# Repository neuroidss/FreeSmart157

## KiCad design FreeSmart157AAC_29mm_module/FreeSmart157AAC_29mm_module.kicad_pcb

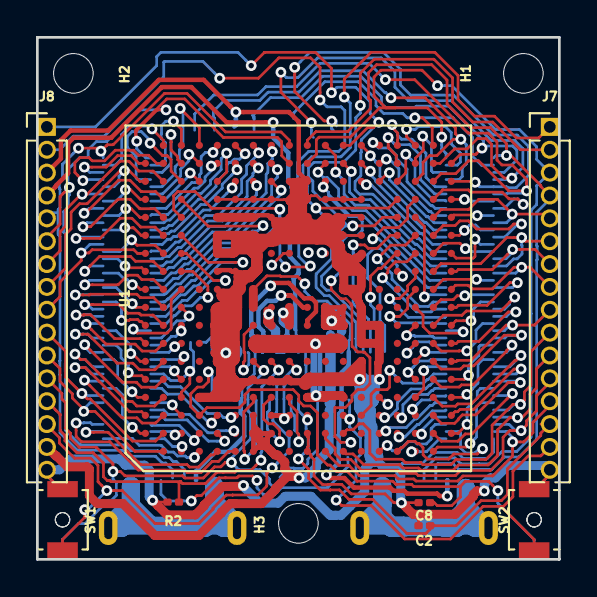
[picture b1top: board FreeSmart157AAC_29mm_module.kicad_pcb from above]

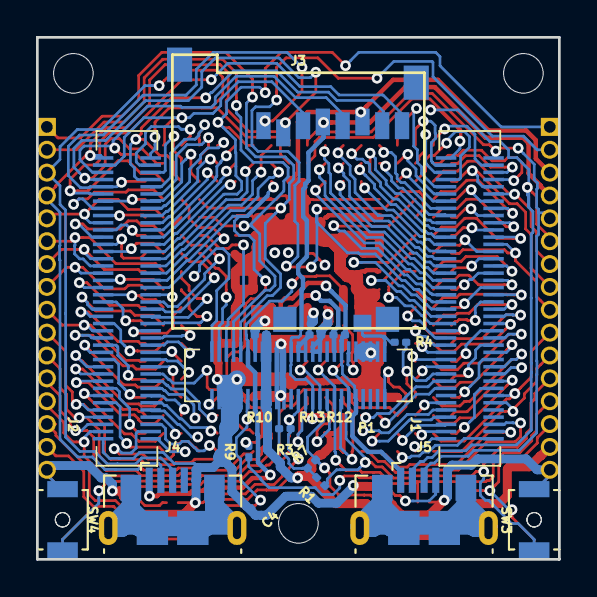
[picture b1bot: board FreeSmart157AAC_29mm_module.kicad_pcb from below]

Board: 2 copper layers, 29.0 x 29.0 mm, 28 parts (17 on the bottom side), 184 nets.

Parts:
C2: 100n; C_0201_0603Metric
C4, C8: 10n; C_0201_0603Metric
H1, H2, H3: MountingHole; MountingHole_2.2mm_M2
J1, J2: Conn_02x40_Odd_Even; HRS_DF40C-80DS-0.4V(51)
J3: 473521001
J4, J5: USB_B_Micro; USB_Micro-B_GCT_USB3076-30-A
J7, J8: Conn_01x16; PinHeader_1x16_P1.27mm_Vertical
P1: DF40C-50DS-0.4V(51); HRS_DF40C-50DS-0.4V(51)
R1, R2, R7: 1k; R_0201_0603Metric
R3, R4, R9, R10, R12, R13: 0; R_0201_0603Metric
SW1: SW_BOOT0; SW_SPST_B3U-1000P-B
SW2: SW_NRST; SW_SPST_B3U-1000P-B
SW3: SW_BOOT2; SW_SPST_B3U-1000P-B
SW4: SW_PMIC_PONKEYN; SW_SPST_B3U-1000P-B
U1: OSD32MP157C-512M-BAA; OSD32MP15x_BGA-302_19.0x19.0mm_Layout18x18_P1.0mm_Ball0.5mm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

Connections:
3V3: J3.4, J8.4, P1.22, P1.27, U1.H3, U1.J3
5V_VIN: J8.15, P1.33, P1.34, P1.35, P1.36, R10.1, U1.G1, U1.G2, U1.G3, U1.H1, U1.H2
A2: J1.15, U1.A2
A3: J1.19, U1.A3
A4: J1.23, U1.A4
A5: J1.27, U1.A5
A6: J1.31, U1.A6
A7: J1.35, U1.A7
A8: J1.39, U1.A8
A9: J1.43, U1.A9
A10: J1.47, U1.A10
A11: J1.51, U1.A11
A12: J1.55, J8.9, U1.A12
A13: J1.59, U1.A13
A14: J1.63, U1.A14
A15: J1.67, U1.A15
A16: J1.71, J8.8, U1.A16
A17: J1.75, U1.A17
B1: J1.11, J8.11, U1.B1
B2: J1.13, J8.10, U1.B2
B3: J1.17, U1.B3
B4: J1.21, U1.B4
B5: J1.25, U1.B5
B6: J1.29, U1.B6
B7: J1.33, U1.B7
B8: J1.37, U1.B8
B9: J1.41, U1.B9
B10: J1.45, U1.B10
B11: J1.49, U1.B11
B12: J1.53, U1.B12
B13: J1.57, U1.B13
B14: J1.61, U1.B14
B15: J1.65, U1.B15
B16: J1.69, J8.7, U1.B16
B17: J1.73, U1.B17
B18: J1.77, U1.B18
C1: J1.2, U1.C1
C2: J1.4, U1.C2
C3: J1.12, U1.C3
C4: J1.20, R4.2, U1.C4
C5: J1.22, U1.C5
C6: J1.24, U1.C6
C7: J1.26, U1.C7
C8: J1.28, U1.C8
C9: J1.30, U1.C9
C10: J1.32, U1.C10
C11: J1.34, U1.C11
C12: J1.36, U1.C12
C13: J1.38, U1.C13
C14_PG11_UART4_TX: J1.40, J8.2, U1.C14
C15: J1.42, U1.C15
C16: J1.74, U1.C16
C17: J1.76, U1.C17
C18: J1.78, U1.C18
D1: J1.1, U1.D1
D2: J1.6, U1.D2
D16: J1.68, U1.D16
D17: J1.70, U1.D17
D18: J1.72, U1.D18
E1: J1.3, U1.E1
E2: J1.8, U1.E2
E3: J1.16, U1.E3
E16: J1.62, U1.E16
E17: J1.64, U1.E17
E18: J1.66, U1.E18
F1: J1.5, U1.F1
F2: J1.10, U1.F2
F3: J1.18, U1.F3
F16: J1.56, U1.F16
F17: J1.58, U1.F17
F18: J1.60, U1.F18
G6_BOOT2: J8.12, P1.12, R1.1, SW3.1, U1.G6
G16: J1.50, U1.G16
G17: J1.52, U1.G17
G18: J1.54, U1.G18
H6_BOOT1: J8.13, P1.16, R2.1, U1.H6
H16: J1.44, U1.H16
H17: J1.46, U1.H17
H18: J1.48, U1.H18
J6_BOOT0: J8.14, P1.20, R7.1, SW1.1, U1.J6
J17_USB_DM2: J1.80, J5.2, J8.6, U1.J17
J18_USB_DP2: J1.79, J5.3, J8.5, U1.J18
K1_VSSA: C2.2, C4.2, C8.2, J2.2, J3.6, J4.5, J5.5, J7.16, J8.3, J8.16, P1.3, P1.5, P1.7, P1.9, P1.42, P1.44, P1.46, P1.48, R2.2, SW1.2, SW2.2, SW3.2, SW4.2, U1.D4, U1.E4, U1.E5, U1.E6, U1.E7, U1.E8, U1.E9, U1.E10, U1.E11, U1.E12, U1.E13, U1.E14, U1.E15, U1.F4, U1.F5, U1.F6, U1.F7, U1.F8, U1.F9, U1.F10, U1.F11, U1.F12, U1.F13, U1.F14, U1.F15, U1.G5, U1.G11, U1.G12, U1.G13, U1.G14, U1.G15, U1.H5, U1.H13, U1.H14, U1.H15, U1.J5, U1.J13, U1.J14, U1.J15, U1.J16, U1.K1, U1.K2, U1.K5, U1.K13, U1.K14, U1.K15, U1.K16, U1.L5, U1.L13, U1.L14, U1.L15, U1.M5, U1.M10, U1.M11, U1.M12, U1.M13, U1.M14, U1.M15, U1.N5, U1.N6, U1.N7, U1.N8, U1.N9, U1.N10, U1.N11, U1.N12, U1.N13, U1.N14, U1.N15, U1.P5, U1.P6, U1.P7, U1.P8
K3_VBAT: C2.1, J7.14, P1.26, R3.1, U1.K3
K9_OTG_VBUS: P1.15, R12.2, U1.K9
K17_USB_DP1: J2.79, J4.3, J7.3, U1.K17
K18_USB_DM1: J2.80, J4.2, J7.4, U1.K18
L1_ANA0: J2.4, J7.13, U1.L1
L2_ANA1: J2.6, J7.12, U1.L2
L16: J2.45, R9.2, U1.L16
L17: J2.47, U1.L17
L18: J2.49, U1.L18
M1_VDDA: J2.8, J7.11, U1.M1
M2_VREF+: J2.10, J7.10, U1.M2
M3_NRST: C4.1, J7.15, P1.40, SW2.1, U1.M3
M17: J2.51, U1.M17
M18_PB2_UART4_RX: J2.53, J8.1, U1.M18
N3: J2.19, U1.N3
N16_DSI_CKP: J2.55, U1.N16
N17_DSI_D1P: J2.57, U1.N17
N18_DSI_D1N: J2.59, U1.N18
P1: J2.5, U1.P1
P2: J2.11, U1.P2
P3: J2.17, U1.P3
P4_EEPROM_WP: P1.50, U1.P4
P16_DSI_CKN: J2.61, U1.P16
P17_DSI_D0P: J2.63, U1.P17
P18_DSI_D0N: J2.65, U1.P18
PMIC_BSTIN: P1.37, R10.2, U1.L8, U1.L9, U1.M8, U1.M9
PMIC_BSTOUT: P1.23, P1.25, R13.1, U1.J8, U1.J9
PMIC_LDO1: P1.24, U1.J4
PMIC_LDO2: P1.14, U1.G4
PMIC_LDO5: P1.11, U1.G8
PMIC_LDO6: P1.18, U1.H4
PMIC_PONKEYN: C8.1, P1.2, SW4.1, U1.D3
PMIC_SWIN: P1.19, P1.21, R13.2, U1.H8, U1.H9
PMIC_SWOUT: J4.1, P1.38, P1.39, U1.G9, U1.G10
PMIC_VBUSOTG: J5.1, P1.10, P1.13, R12.1, U1.K8
R1: J2.3, U1.R1
R2: J2.9, U1.R2
R3: J2.15, U1.R3
R11_NJTRST: P1.49, U1.R11
R12_JTDO-TRACESWO: P1.47, U1.R12
R13_JTDI: P1.45, U1.R13
R14_JTMS-SWDIO: J7.2, P1.43, U1.R14
R15_JTCK-SWCLK: J7.1, P1.41, U1.R15
R16: J2.67, U1.R16
R17: J2.69, U1.R17
R18: J2.71, U1.R18
SDMMC1_DETECT: J3.9, P1.1, R4.1
T1: J2.1, U1.T1
T2: J2.7, U1.T2
T3: J2.13, U1.T3
T4: J2.21, U1.T4
T5: J2.23, U1.T5
T6: J2.25, U1.T6
T7: J2.27, U1.T7
T8: J2.29, U1.T8
T9: J2.31, U1.T9
T10: J2.33, U1.T10
T11: J2.35, U1.T11
T12: J2.37, U1.T12
T13: J2.39, U1.T13
T14: J2.41, U1.T14
T15: J2.43, U1.T15
T16_PC8_SDMMC1_D0: J2.73, J3.7, U1.T16
T17: J2.75, U1.T17
T18: J2.77, U1.T18
U1: J2.12, U1.U1
U2: J2.14, U1.U2
U3: J2.18, U1.U3
U4: J2.22, U1.U4
U5: J2.26, U1.U5
U6: J2.30, U1.U6
U7: J2.34, U1.U7
U8: J2.38, U1.U8
U9: J2.42, U1.U9
U10: J2.46, U1.U10
U11: J2.50, J7.6, U1.U11
U12: J2.54, U1.U12
U13: J2.58, U1.U13
U14: J2.62, J7.5, U1.U14
U15: J2.66, U1.U15
U16_PC9_SDMMC1_D1: J2.70, J3.8, U1.U16
U17_PC11_SDMMC1_D3: J2.74, J3.2, U1.U17
U18_PD2_SDMMC1_CMD: J2.78, J3.3, U1.U18
USBID2: J5.4, R9.1
V2: J2.16, U1.V2
V3: J2.20, U1.V3
V4: J2.24, U1.V4
V5: J2.28, U1.V5
V6: J2.32, J7.9, U1.V6
V7: J2.36, U1.V7
V8: J2.40, U1.V8
V9: J2.44, U1.V9
V10: J2.48, J7.8, U1.V10
V11: J2.52, J7.7, U1.V11
V12: J2.56, U1.V12
V13: J2.60, U1.V13
V14: J2.64, U1.V14
V15: J2.68, U1.V15
V16_PC10_SDMMC1_D2: J2.72, J3.1, U1.V16
V17_PC12_SDMMC1_CK: J2.76, J3.5, U1.V17
VDD: P1.29, P1.30, P1.31, P1.32, R1.2, R3.2, R7.2, U1.G7, U1.H7, U1.J7, U1.K4, U1.K7, U1.L4, U1.L7, U1.M4, U1.M7

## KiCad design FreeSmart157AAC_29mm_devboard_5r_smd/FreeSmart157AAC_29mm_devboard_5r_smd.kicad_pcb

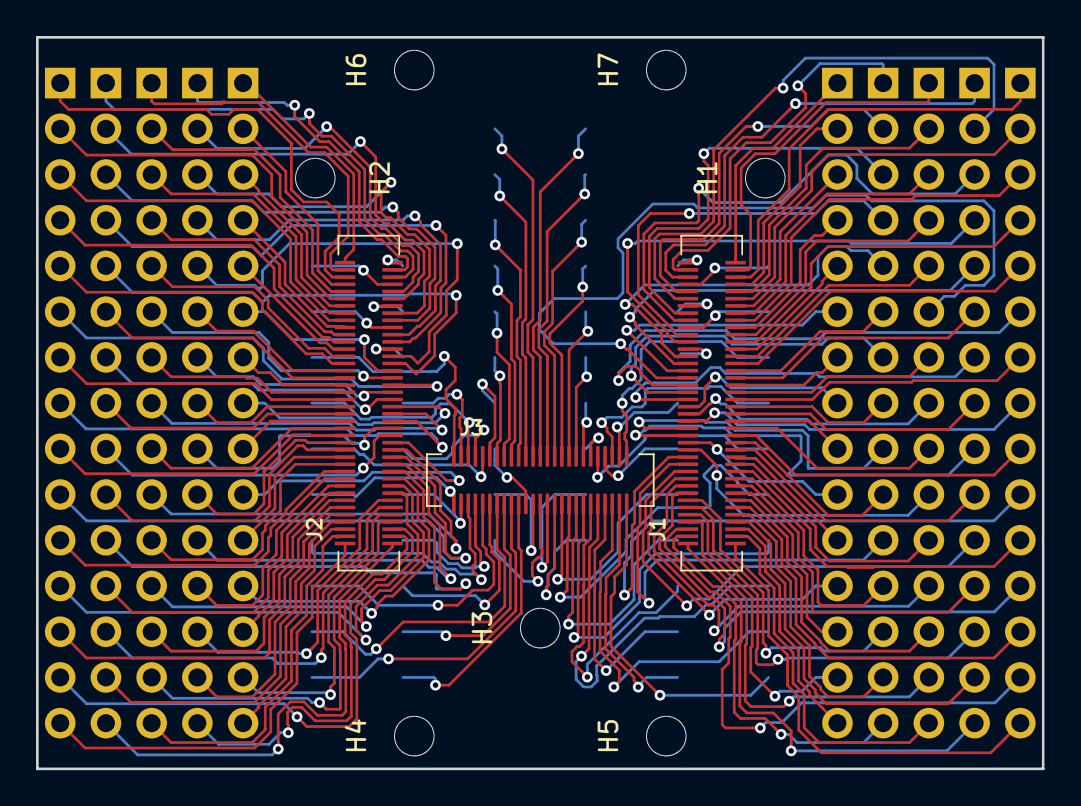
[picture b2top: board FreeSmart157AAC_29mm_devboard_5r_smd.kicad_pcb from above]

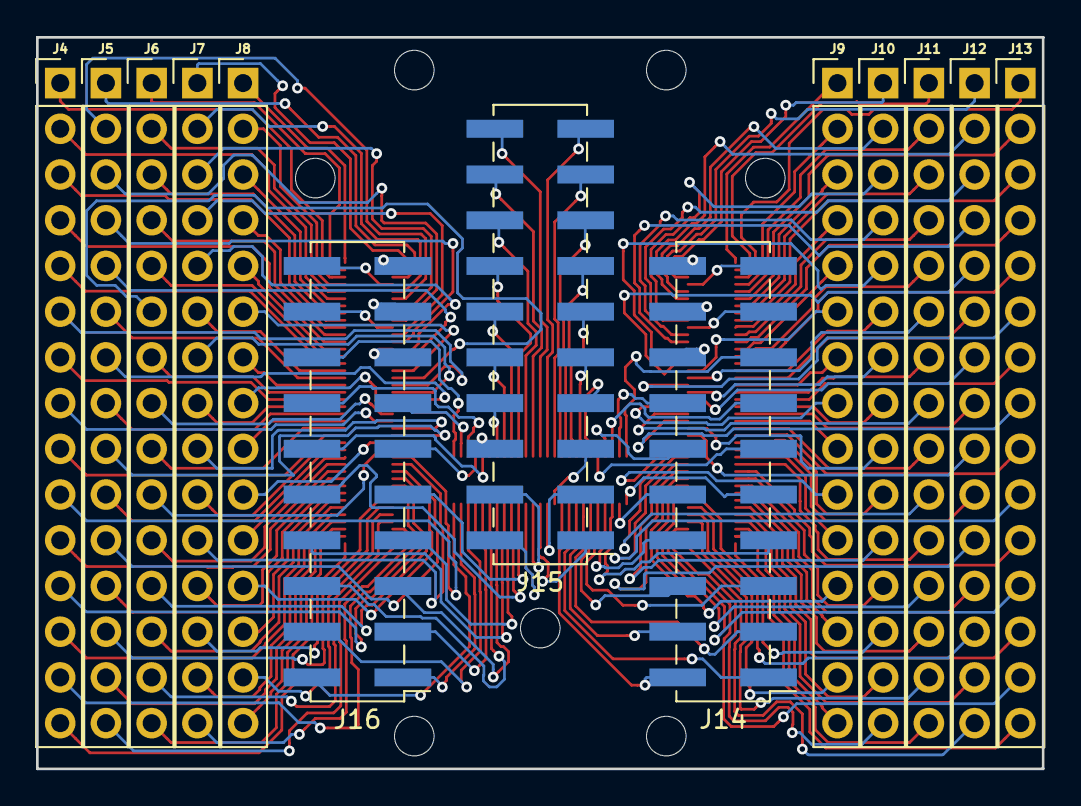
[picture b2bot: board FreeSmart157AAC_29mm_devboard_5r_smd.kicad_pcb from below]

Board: 2 copper layers, 55.9 x 40.6 mm, 23 parts (13 on the bottom side), 210 nets.

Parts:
H1, H2, H3, H4, H5, H6, H7: MountingHole; MountingHole_2.2mm_M2
J1, J2: Conn_02x40_Odd_Even; HRS_DF40C-80DS-0.4V(51)
J3: Conn_02x25_Odd_Even; HRS_DF40C-50DS-0.4V(51)
J4, J5, J6, J7, J8, J9, J10, J11, J12, J13: Conn_01x15; PinHeader_1x15_P2.54mm_Vertical
J14, J15, J16: Conn_02x10_Odd_Even; PinHeader_2x10_P2.54mm_Vertical_SMD

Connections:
A1: J2.79, J14.20
A2: J2.80, J9.1
A3: J2.77, J10.1
A4: J2.78, J11.1
A5: J2.75, J12.1
A6: J2.76, J13.1
A7: J2.73, J14.19
A8: J2.74, J9.2
A9: J2.71, J10.2
A10: J2.72, J11.2
A11: J2.69, J12.2
A12: J2.70, J13.2
A13: J2.67, J14.18
A14: J2.68, J9.3
A15: J2.65, J10.3
A16: J2.66, J11.3
A17: J2.63, J12.3
A18: J2.64, J13.3
A19: J2.61, J14.17
A20: J2.62, J9.4
A21: J2.59, J10.4
A22: J2.60, J11.4
A23: J2.57, J12.4
A24: J2.58, J13.4
A25: J2.55, J14.16
A26: J2.56, J9.5
A27: J2.53, J10.5
A28: J2.54, J11.5
A29: J2.51, J12.5
A30: J2.52, J13.5
A31: J2.49, J9.6
A32: J2.50, J10.6
A33: J2.47, J11.6
A34: J2.48, J12.6
A35: J2.45, J13.6
A36: J2.46, J9.7
A37: J2.43, J10.7
A38: J2.44, J11.7
A39: J2.41, J12.7
A40: J2.42, J13.7
A41: J2.39, J9.8
A42: J2.40, J10.8
A43: J2.37, J11.8
A44: J2.38, J12.8
A45: J2.35, J13.8
A46: J2.36, J9.9
A47: J2.33, J10.9
A48: J2.34, J11.9
A49: J2.31, J12.9
A50: J2.32, J13.9
A51: J2.29, J9.10
A52: J2.30, J10.10
A53: J2.27, J11.10
A54: J2.28, J12.10
A55: J2.25, J13.10
A56: J2.26, J9.11
A57: J2.23, J10.11
A58: J2.24, J11.11
A59: J2.21, J12.11
A60: J2.22, J13.11
A61: J2.19, J9.12
A62: J2.20, J10.12
A63: J2.17, J11.12
A64: J2.18, J12.12
A65: J2.15, J13.12
A66: J2.16, J9.13
A67: J2.13, J10.13
A68: J2.14, J11.13
A69: J2.11, J12.13
A70: J2.12, J13.13
A71: J2.9, J9.14
A72: J2.10, J10.14
A73: J2.7, J11.14
A74: J2.8, J12.14
A75: J2.5, J13.14
A76: J2.6, J9.15
A77: J2.3, J10.15
A78: J2.4, J11.15
A79: J2.1, J12.15
A80: J2.2, J13.15
B1: J1.80, J16.19
B2: J1.79, J8.1
B3: J1.78, J7.1
B4: J1.77, J6.1
B5: J1.76, J5.1
B6: J1.75, J4.1
B7: J1.74, J16.20
B8: J1.73, J8.2
B9: J1.72, J7.2
B10: J1.71, J6.2
B11: J1.70, J5.2
B12: J1.69, J4.2
B13: J1.68, J16.17
B14: J1.67, J8.3
B15: J1.66, J7.3
B16: J1.65, J6.3
B17: J1.64, J5.3
B18: J1.63, J4.3
B19: J1.62, J16.18
B20: J1.61, J8.4
B21: J1.60, J7.4
B22: J1.59, J6.4
B23: J1.58, J5.4
B24: J1.57, J4.4
B25: J1.56, J16.15
B26: J1.55, J8.5
B27: J1.54, J7.5
B28: J1.53, J6.5
B29: J1.52, J5.5
B30: J1.51, J4.5
B31: J1.50, J8.6
B32: J1.49, J7.6
B33: J1.48, J6.6
B34: J1.47, J5.6
B35: J1.46, J4.6
B36: J1.45, J8.7
B37: J1.44, J7.7
B38: J1.43, J6.7
B39: J1.42, J5.7
B40: J1.41, J4.7
B41: J1.40, J8.8
B42: J1.39, J7.8
B43: J1.38, J6.8
B44: J1.37, J5.8
B45: J1.36, J4.8
B46: J1.35, J8.9
B47: J1.34, J7.9
B48: J1.33, J6.9
B49: J1.32, J5.9
B50: J1.31, J4.9
B51: J1.30, J8.10
B52: J1.29, J7.10
B53: J1.28, J6.10
B54: J1.27, J5.10
B55: J1.26, J4.10
B56: J1.25, J8.11
B57: J1.24, J7.11
B58: J1.23, J6.11
B59: J1.22, J5.11
B60: J1.21, J4.11
B61: J1.20, J8.12
B62: J1.19, J7.12
B63: J1.18, J6.12
B64: J1.17, J5.12
B65: J1.16, J4.12
B66: J1.15, J8.13
B67: J1.14, J7.13
B68: J1.13, J6.13
B69: J1.12, J5.13
B70: J1.11, J4.13
B71: J1.10, J8.14
B72: J1.9, J7.14
B73: J1.8, J6.14
B74: J1.7, J5.14
B75: J1.6, J4.14
B76: J1.5, J8.15
B77: J1.4, J7.15
B78: J1.3, J6.15
B79: J1.2, J5.15
B80: J1.1, J4.15
C1: J3.2, J14.15
C2: J3.1, J14.9
C3: J3.4, J14.14
C4: J3.3, J14.10
C5: J3.6, J14.13
C6: J3.5, J14.7
C7: J3.8, J14.12
C8: J3.7, J14.8
C9: J3.10, J14.11
C10: J3.9, J14.5
C11: J3.12, J15.7
C12: J3.11, J14.6
C13: J3.14, J15.9
C14: J3.13, J14.3
C15: J3.16, J15.11
C16: J3.15, J14.4
C17: J3.18, J15.13
C18: J3.17, J14.1
C19: J3.20, J15.15
C20: J3.19, J14.2
C21: J3.22, J15.17
C22: J3.21, J15.5
C23: J3.24, J15.19
C24: J3.23, J15.3
C25: J3.26, J15.20
C26: J3.25, J15.1
C27: J3.28, J15.18
C28: J3.27, J15.4
C29: J3.30, J15.16
C30: J3.29, J15.2
C31: J3.32, J15.14
C32: J3.31, J16.9
C33: J3.34, J15.12
C34: J3.33, J16.10
C35: J3.36, J15.10
C36: J3.35, J16.7
C37: J3.38, J15.8
C38: J3.37, J16.8
C39: J3.40, J15.6
C40: J3.39, J16.5
C41: J3.42, J16.12
C42: J3.41, J16.6
C43: J3.44, J16.11
C44: J3.43, J16.3
C45: J3.46, J16.14
C46: J3.45, J16.4
C47: J3.48, J16.13
C48: J3.47, J16.1
C49: J3.50, J16.16
C50: J3.49, J16.2
